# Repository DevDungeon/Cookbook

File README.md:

## The Cookbook Method

A cookbook in the programming context is collection of tiny programs that each demonstrate a particular programming concept. The Cookbook Method is the process of learning a programming language by building up a repository of small programs that implement specific programming concepts. Starting with a Hello World program and building the knowledge piece by piece on top of that.

If you are a beginner, you will probably want to start out with one language like Python and start building up your repetoire of snippets for reference and confidence. If you are a seasoned developer, you may want to start building a cookbook from scratch for a new language you have never used, or keep a cookbook for more advanced topics in a language you are already familiar with.

Here is an example of when my Cookbook comes in handy. Recently I was faced with a situation where I needed to make an HTTP request to an API, parse the JSON response, generate a CSV spreadsheet, and email the spreadsheet. Because I already had my own cookbook snippets for doing each of those three actions, it was really easy to put together a program that did what I needed it to.

## Watch the video

### Benefits of Building Your Own Cookbook

* You can share it with others
* Learn topics that are interesting to you
* You build up your knowledge in small increments
* You can see your progress over time
* You have a library of reference material in your own style.
* It is quicker than looking up documentation or looking for a Stack Overflow answer.
* Explore new topics
* Learn new programming languages.
* Tips for Building a Cookbook
* Store your cookbook in a version control system like Git.
* Keep a to do list of topics or programming languages you want to explore and learn
* It does not have to be just code. I have a lot of plain text .txt files with notes on things like how to create a Python pip package, creating Ruby Gems, or how to create a runnable JAR in Java. Sometimes tips on installing prerequisites if something was difficult or just notes on how to compile and run programs.
* It can also be template programs. For example I have a base chrome browser extension that doesn't really do anything itself, but it is a fully functional extension with all the boilerplate done and ready for me to start developing.
* Programs should be fully runnable and not just chunks of code without context that do not compile and execute
* Keep the snippets small, simple and to one topic

### Example Cookbook Topics

Everyone has different goals with programming so identify topics relevant to your interests. Here are some ideas if you do not know where to get started.

* Hello, world
* Getting user input from stdin
* Taking command line arguments
* Reading and writing files
* Using TCP sockets
* Making HTTP requests
* Parsing JSON
* Creating a CSV file
* Making database connections
* Playing an audio file
* Multithreading
* Drawing 2D graphics to screen
* Drawing 3D graphics to screen
* GUI programming

## The DevDungeon Cookbook

* http://www.devdungeon.com/cookbook
* https://github.com/DevDungeon/Cookbook

## Contact

John "NanoDano" Leon <nanodano@devdungeon.com>
https://www.devdungeon.com

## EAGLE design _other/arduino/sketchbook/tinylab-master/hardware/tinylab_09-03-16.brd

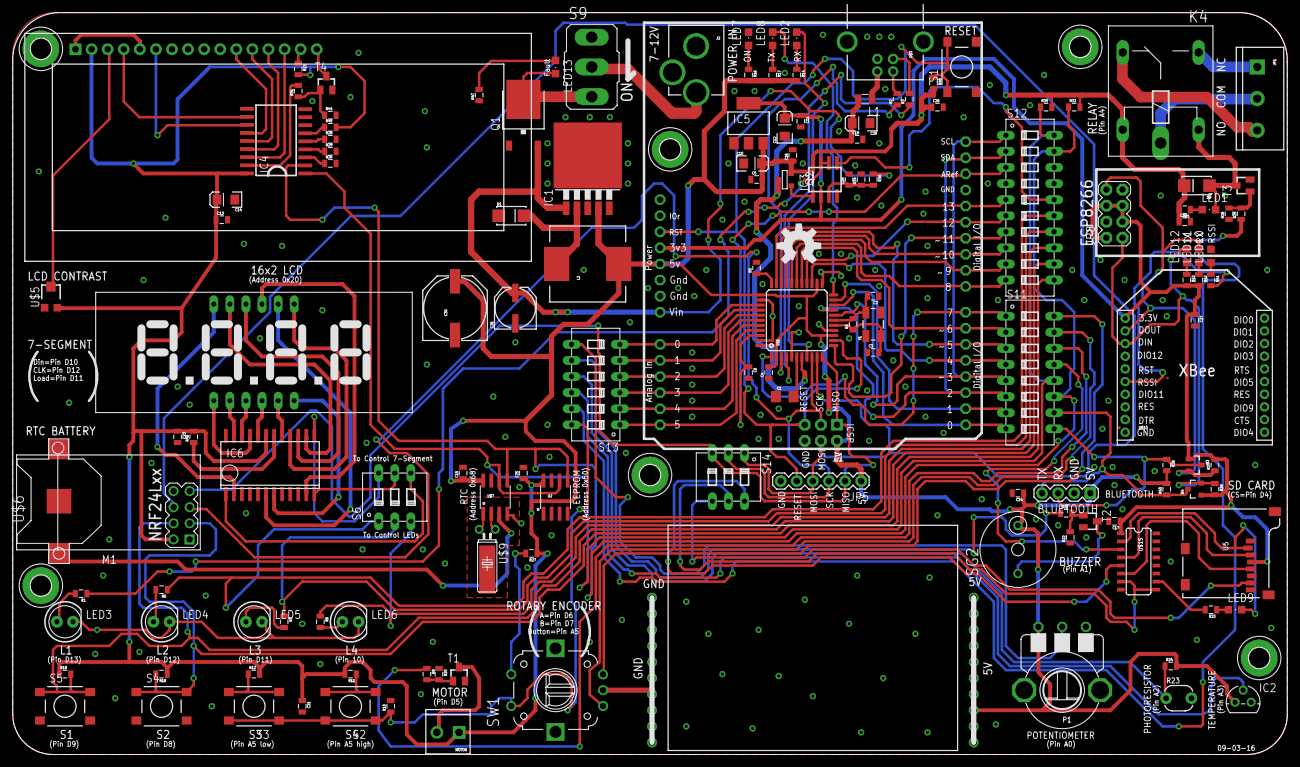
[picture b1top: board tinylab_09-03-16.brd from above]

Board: 2 copper layers, 201.3 x 117.2 mm, 151 parts (0 on the bottom side), 136 nets.

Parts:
BLUETOOTH: 1X04
C1: 1uF; 1206
C2, C3: 22pF; 0805
C4, C5, C6, C11, C15, C16, C17, C18, C19, C21, C22, C24, C25, C26, C27: 100nF; 0805
C10, C12, C20: 10uF; EIA3216
C13, C23: 100nf; 0805
C14: 10uf; EIA3216
C28: 100uF; NIPPON_F80
C30: 470uF; PANASONIC_G
D1, D2: 1N4007; SMA-DIODE_ALT
H1, H2, H3, H4, H5, H6: MOUNT-PAD-ROUND3.2; 3,2-PAD
IC1: LM2575S; TO263-5
IC2: LM35CZ; TO92
IC3: LM358MX; SO08
IC4: MCP2300X/SO; SO18W
IC5: LD117AS33TR; SOT223
IC6: MAX7219CWG; SO24W
J1: AVR_SPI_PRG_6NS; 2X3-NS
J2: POWER_JACKPTH_LOCK; POWER_JACK_PTH_LOCK
JP1: SCREWTERMINAL-5MM-3
JP5: 1X06
JP8: 2X4
K4: ZF112
L1: PTC0805
L2: CDRH125
LED1, LED9, LED12: Blue; CHIPLED_0805
LED2, LED8: Green; CHIPLED_0805
LED3, LED4, LED5, LED6: RED; LED5MM
LED7, LED10: Yellow; CHIPLED_0805
LED11, LED13: Red; CHIPLED_0805
M1: WIRELESS-NRF24L01
MOTOR: SCREWTERMINAL-3.5MM-2
P1: P120PK
Q1: FDD4141 or FDD6637; TO252
Q2: FDN340; SOT-23
Q3, Q4: BSS138; SOT23-3
R1, R6, R7, R8, R14, R16, R17: 330; 0805
R2, R3: 22; 0805
R4: 1M; 0805
R5, R34, R36, R37, R38, R39, R40: 10K; 0805
R9, R10, R11, R15, R21, R25, R31, R33, R47: 1k; 0805
R12: 3.9k; 0805
R13: 100R; 0805
R18, R19, R20, R22, R24, R26, R27, R28, R29, R30, R44, R45, R48: 10k; 0805
R23: PHOTOCELLPTH-KIT; PHOTOCELL-KIT
R32, R35: 4.7k; 0805
R41, R42, R43: 1K; 0805
R46: 30k; 0805
S1, S2, S3, S4, S5: DTSM-6
S6, S14: DIP03YL
S9: M9040P
S11: DIP08YL
S12: DIP10YL
S13: DIP06YL
SG2: BMT1205XH7.5
SW1: ENCODER_SW1-PEC12; PEC12_INCREMENTAL_ENCODER
T1, T2, T3, T4: BC847; SOT23-BEC
U1: LCD-16X2SILK; LCD-16X2
U2: 24LC256; SO08
U5: USD-SOCKETNEW; MICRO-SD-SOCKET-PP
U$1: ATMEGA32U4TQFP-44; TQFP44
U$2: BREADBOARDMINI; BREADBOARD-MINI
U$3: USB+SHIELD; USB-B-PTH
U$4: UNO_R3
U$5: 10k; TC33X
U$6: CR1220-SMD
U$7: DS1307SO8; SO08
U$9: CRYSTAL_GNDPAD; TC38H_GNDPAD
U$10: XBEE-1B2; XBEE-SILK
U$11: TINYLAB_LOGO_LARGE
U$13: MYLIB_LCQ_4D_7SEG; MYLIB_LDQ_4D_7SEG
U$14: OSHW-LOGO-L
U$15: 74HC4050; SO016
Y1: 16Mhz; CRYSTAL-SMD-5X3

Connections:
3.3V: C11.1, C12.A, C17.1, C27.1, IC3.2, IC5.4, JP8.2, JP8.3, JP8.5, JP8.6, Q3.1, Q4.1, R37.2, R39.2, R42.2, R43.2, U5.4, U$4.3V, U$10.1, U$15.1
4: S11.4, U$1.25, U$4.D4
5: S11.3, U$1.31, U$4.D5
6: S11.2, U$1.27, U$4.D6
7: S11.1, U$1.1, U$4.D7
8: S12.10, U$1.28, U$4.D8
9: S12.9, U$1.29, U$4.D9
10: S12.8, U$1.30, U$4.D10
11: S12.7, U$1.12, U$4.D11
12: S12.6, U$1.26, U$4.D12
13: S12.5, U$1.32, U$4.D13
!RESET: J1.5, JP5.5, R48.1, S1.1, S1.2, U$1.13, U$4.RESET
+5V: BLUETOOTH.1, C4.2, C5.2, C10.A, C13.1, C14.A, C15.1, C16.1, C21.1, C22.1, C23.1, C24.1, C25.1, C26.1, C30.+, D2.C, IC1.4, IC2.1, IC3.8, IC4.18, IC5.3, IC6.19, J1.2, JP5.1, K4.1, L2.2, M1.2, MOTOR.1, P1.E, Q2.2, R11.2, R12.2, R13.2, R14.2, R15.2, R16.2, R17.2, R18.1, R19.1, R24.2, R27.1, R32.2, R35.2, R38.2, R40.2, R45.2, R46.2, R48.2, SG2.+, U1.2, U2.8, U$1.2, U$1.14, U$1.24, U$1.34, U$1.44, U$4.5V, U$5.3, U$7.8
A0: P1.S, S13.7
A1: R21.1, S13.8
A2: R23.1, R24.1, S13.9
A3: IC2.2, S13.10
A4: R25.1, S13.11
A5: R10.1, S2.1, S2.2, S3.1, S3.2, S13.12, SW1.P1
A_A0: S13.6, U$1.36, U$4.A0
A_A1: S13.5, U$1.37, U$4.A1
A_A2: S13.4, U$1.38, U$4.A2
A_A3: S13.3, U$1.39, U$4.A3
A_A4: S13.2, U$1.40, U$4.A4
A_A5: S13.1, U$1.41, U$4.A5
A_AREF: C6.1, S12.3, U$1.42, U$4.AREF
A_MISO: J1.1, JP5.2, M1.7, S14.3, U$1.11
A_MOSI: J1.4, JP5.4, M1.6, S14.1, U$1.10
A_RX: S11.8, U$1.20, U$4.D0
A_SCK: J1.3, JP5.3, M1.5, S14.2, U$1.9
A_SCL: S11.5, S12.1, U$1.18, U$4.D3, U$4.SCL
A_SDA: S11.6, S12.2, U$1.19, U$4.D2, U$4.SDA
A_TX: S11.7, U$1.21, U$4.D1
D4: S11.13, U$15.3
D5: R9.1, S11.14
D6: S11.15, SW1.A
D7: S11.16, SW1.B
D8: M1.3, R18.2, S4.1, S4.2, S12.11
D9: M1.4, R19.2, S5.1, S5.2, S12.12
D10: R8.1, S6.3, S12.13
D11: R7.1, S6.2, S12.14
D12: R6.1, S6.1, S12.15
D13: IC3.5, S12.16
D+: R3.1, U$1.4
D-: R2.1, U$1.3
DB4: IC4.13, U1.11
DB5: IC4.14, U1.12
DB6: IC4.15, U1.13
DB7: IC4.16, U1.14
DIN: JP8.1, LED12.C, Q4.2, R39.1, U$10.3
DOUT: JP8.8, LED11.C, Q3.2, R37.1, U$10.2
E: IC4.12, U1.6
GND: BLUETOOTH.2, C1.1, C2.1, C3.1, C4.1, C5.1, C6.2, C10.C, C11.2, C12.C, C13.2, C14.C, C15.2, C16.2, C17.2, C18.2, C19.2, C20.C, C21.2, C22.2, C23.2, C24.2, C25.2, C26.2, C27.2, C28.-, C30.-, D1.A, IC1.3, IC1.5, IC1.GND, IC2.3, IC3.4, IC4.9, IC5.1, IC6.4, IC6.9, J1.6, J2.GND, J2.GNDBREAK, JP5.6, JP8.7, LED3.K, LED4.K, LED5.K, LED6.K, LED7.C, LED10.C, M1.1, P1.A, Q1.1, R5.2, R10.2, R20.1, R22.1, R23.2, R26.1, R28.2, R29.2, R30.2, R34.2, R44.2, R47.1, S1.3, S1.4, S4.3, S4.4, S5.3, S5.4, S12.4, S12.17, SW1.C, T1.E, T2.E, T3.E, T4.E, U1.1, U1.5, U2.1, U2.2, U2.3, U2.4, U2.7, U5.6, U5.CD1, U5.CD2, U5.GND1, U5.GND3, U$1.5, U$1.15, U$1.23, U$1.35, U$1.43, U$3.GND, U$3.S1, U$3.S2, U$4.GND, U$4.GND1, U$4.GND2, U$5.1, U$6.-, U$7.4, U$9.P$1, U$10.10, U$15.8, U$15.11, U$15.14
LED: R33.2, U$15.10
LIGHT: IC4.17, R31.2
MISO: S14.4, U5.7
MOSI: S14.6, U$15.5
unnamed: R2.2, U$3.D-
unnamed: R3.2, U$3.D+
unnamed: LED3.A, R1.2
unnamed: C1.2, U$1.6
unnamed: R11.1, S2.3, S2.4
unnamed: C3.2, R4.1, U$1.16, Y1.1
unnamed: C2.2, R4.2, U$1.17, Y1.3
unnamed: R21.2, R22.2, T2.B
unnamed: R5.1, U$1.33
unnamed: D1.C, IC1.2, L2.1
unnamed: R12.1, S3.3, S3.4
unnamed: R9.2, R20.2, T1.B
unnamed: LED4.A, R6.2
unnamed: JP1.3, K4.O
unnamed: LED5.A, R7.2
unnamed: MOTOR.2, T1.C
unnamed: LED6.A, R8.2
unnamed: SG2.-, T2.C
unnamed: LED1.A, R15.1
unnamed: R25.2, R26.2, T3.B
unnamed: D2.A, K4.2, LED1.C, T3.C
unnamed: LED2.A, R14.1
unnamed: LED8.A, R17.1
unnamed: JP1.2, K4.P
unnamed: JP1.1, K4.S
unnamed: J2.PWR, S9.2
unnamed: LED13.C, Q1.3, S9.3
unnamed: IC4.5, R28.1
unnamed: IC4.4, R29.1
unnamed: IC4.3, R30.1
unnamed: R27.2, SW1.P2
unnamed: R31.1, R44.1, T4.B
unnamed: U1.3, U$5.2
unnamed: T4.C, U1.16
unnamed: U$7.2, U$9.1
unnamed: U$6.+$1, U$7.3
unnamed: IC6.14, U$13.11
unnamed: U5.3, U$15.4
unnamed: U5.5, U$15.6
unnamed: U$7.1, U$9.2
unnamed: LED9.A, R33.1
unnamed: LED9.C, U5.2, U$15.2
unnamed: L1.1, U$3.VBUS
unnamed: C18.1, IC3.3, R34.1, R36.2
unnamed: LED10.A, R41.1
unnamed: IC3.1, Q2.3
unnamed: IC3.6, IC3.7, R1.1
unnamed: LED11.A, R42.1
unnamed: LED12.A, R43.1
unnamed: LED13.A, R47.2
unnamed: IC4.6, R45.1
unnamed: IC6.18, R46.1
unnamed: IC6.16, U$13.7
unnamed: IC6.20, U$13.4
unnamed: IC6.23, U$13.2
unnamed: IC6.21, U$13.1
unnamed: IC6.15, U$13.10
unnamed: IC6.17, U$13.5
unnamed: IC6.22, U$13.3
unnamed: IC6.7, U$13.6
unnamed: IC6.6, U$13.8
unnamed: IC6.11, U$13.9
unnamed: IC6.2, U$13.12
unnamed: R13.1, U1.15
unnamed: LED7.A, R16.1
RS: IC4.11, U1.4
RSSI: R41.2, U$10.6
RX: BLUETOOTH.3, Q3.3, R38.1, S11.9
RXLED: LED2.C, U$1.8
SCK: S14.5, U$15.7, U$15.9
SCL: IC4.1, R35.1, S11.12, S12.20, U2.6, U$7.6
SDA: IC4.2, R32.1, S11.11, S12.19, U2.5, U$7.5
S_D10: IC6.1, S6.4
S_D11: IC6.12, S6.5
S_D12: IC6.13, S6.6
TX: BLUETOOTH.4, Q4.3, R40.1, S11.10
TXLED: LED8.C, U$1.22
VCC: C28.+, IC1.1, Q1.2, R36.1, U$4.VIN
VUSB: C19.1, C20.A, L1.2, Q2.1, U$1.7

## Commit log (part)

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2015-04-22 Initial commit. Adding all reference code under one repo
2015-04-26 Adding python blackhat udp and ping discovery
2015-04-26 Adding git ignore in python to ignore .idea folder
2015-04-26 Adding sys_info.py with system info like platform, variable sizes, etc
2015-05-07 Adding gitignore to php drupal modules bitcoin_donation phpqrcode cache folder
2015-05-17 Adding android studio project files
2015-07-29 Adding a couple more samples
2015-08-14 Updating Ruby daemon example
2015-08-14 Adding file and dir manipulation in perl example
2015-08-14 Updating perl exif example
2015-08-14 Updating hello world perl
2015-08-14 Adding image examples
2015-08-14 Updating haskell cmd arg example
2015-08-14 Updated coffeescript references
2015-08-14 Adding simplified webrtc audio example
2015-08-16 Adding updating C Pcap examples
2015-08-16 Updating packet capture examples with gopacket
2015-08-23 Adding file examples
2015-08-23 Updated file examples in Go
2015-09-20 misc updates. Removed chrome extension base since it is its own repo now
2015-09-20 Cleaning up some snippets. Updated bash references
2015-11-23 Adding references for binary data in python
2015-11-24 Adding some Perl HTTP and DOM references
2015-12-06 Adding Python Tkinter references
2015-12-09 Adding readme
2015-12-21 Adding my LAMP dashboard written in Python/GTK/Glade as an example
2015-12-24 Cleaning up and renaming a couple things
2016-01-02 Updating Python examples
2016-01-02 Adding some Java examples
2016-01-02 Adding example of a Java Jar with resources like images
2016-01-02 updating git ignore
2016-01-02 Adding SSH example with Jsch
2016-01-02 Adding Excel files example using POI
2016-01-02 Adding two examples: RedditClient which uses Apache Http client along with org.json library. SimpleJson is the same thing except uses the google code simple json library. They are similar not sure if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
2016-01-10 Maven project demonstrating how to create a mac .app
2016-01-15 Adding another simple SSL server example
2016-01-31 Adding example for Russian espeak text to speech
2016-02-01 Adding some basic Rust notes
2016-04-13 Adding some C++ Examples: sleep, random, ncurses, qt5+winpcap. Also Python ldap server example
2016-04-14 Adding compilation notes
2016-04-14 Minimal C example from the C bible
2016-04-16 Adding examples to count characters and lines
2016-04-16 Adding example of counting words, lines, and characters]
2016-04-16 Adding more C examples
2016-04-16 Even more C examples
2016-04-17 Fix bug in qsort output and add void pointer cast example.
2016-04-23 Adding some bindshell examples and info on adding Icon to Windows GCC .exe
2016-05-08 Adding misc snippets that were laying around
2016-07-16 Adding spreadsheet examples with CSV and XLSX
2016-07-22 Adding selenium screenshot examples
2016-07-31 Adding Android examples: contact list, disk space checker. Go mongo example, python selenium and extract pngs from binary files. Python spreadsheet examples. Ruby selenium example
2016-10-06 Updating Java Pcap example so the maven file creates a jar and a shaded(uber) jar so it runs as a standalone
2016-10-06 Changing required jvm from 1.8 to 1.7 in 2d example
2016-10-14 Adding ability to use multiple icons and let the JVM decide on the best.
2016-10-14 Adding Desktop Demos
2016-10-15 Adding latest examples
2016-11-18 Tweaks
2016-11-18 Adding some neopixel examples
2016-12-02 Updating Python Selenium screenshot example. Updating Java SSH examples
2017-10-20 Adding Philips Hue light programming notes. Updated notes for static compiling Go programs for Docker containers
2017-10-21 Adding BitCoin Python price checker and Discord Bot Webhook example
2018-02-20 Adding discord bot example
2018-02-24 Updating samples
2018-03-05 Notes
2018-03-05 Adding new c++ stuff
2018-03-05 Adding make and cmake examples
2018-03-05 Adding simple libfunctions library example
2018-03-06 Adding c++ examples
2018-03-10 Adding bytes examples
2018-03-25 Adding Go web scraping examples
2018-03-25 Adding new C++ examples
2018-07-14 Adding AWS, OpenSCAD, Raspberry Pi, and Python example!
2018-09-11 Updaing notes about managing letsencrypt certs
2018-09-11 Adding JS Discord bot examples
2018-10-02 Adding Python text-to-speech, Java properties files
2018-10-06 Cleaning up Java directory
2018-10-16 Reorganizing, putting more tutorials
2018-10-29 Refactoring
2019-02-16 moving around
2019-02-27 Adding rust cross-compiling example
2019-02-27 Adding Rust/C wrapping and linking examples
2019-02-27 Updating todo list
2019-03-02 Adding python web scraping examples
2019-03-02 Removing incomplete docs
2019-03-20 Adding notes about Crystal language
2019-03-21 Adding cordova notes
2019-03-23 Adding get_file_metadata program
2019-03-23 Adding dump_hex example
2019-03-24 Adding find ascii in file application
2019-03-24 Adding find_file_signatures application
2019-03-29 Adding Selenium notes
2019-04-04 Adding vim notes
2019-04-04 Adding vscode notes
2019-04-10 Adding several examples
    - Python curses examples
    - RAspberry pi timelapse photo taker
    - reStructuredText example
    - Ruby getpass and ssh examples
2019-04-10 Adding Maven m2 settings example for Java
2019-04-24 Added Base64, echoing, functions, aliases
    I also fixed the indentation and spacing in a way that now makes sense. I also posted a link to a documentation website listing all standard Powershell commands.
2019-05-23 Fixing Ruby GTK+3 examples
2019-05-23 Adding qt systray icon and dialog examples
2019-08-20 Adding kivy android notes
2019-09-09 Latest updateS
2019-09-13 Flask examples
2020-02-11 Added wxpython pip notes
2020-03-02 adding python sqlite examples
2020-03-14 adding pymysql examples
2020-03-14 Adding python IMAP read mail examples
2020-03-15 Adding from/to/priority output of reading mail
2020-03-15 Adding Python FTP examples
2020-03-16 Adding Python SSH examples
2020-06-01 Adding log rotate example for Python
2020-06-15 Removing old languages and examples
2020-10-12 Bump junit from 3.8.1 to 4.13.1 in /java/ServletExamples/mvnhelloservlet
    Bumps [junit](https://github.com/junit-team/junit4) from 3.8.1 to 4.13.1.
    - [Release notes](https://github.com/junit-team/junit4/releases)
    - [Changelog](https://github.com/junit-team/junit4/blob/main/doc/ReleaseNotes4.13.1.md)
    - [Commits](https://github.com/junit-team/junit4/commits/r4.13.1)
2020-10-13 Bump junit from 3.8.1 to 4.13.1 in /java/SendMailExample
    Bumps [junit](https://github.com/junit-team/junit4) from 3.8.1 to 4.13.1.
    - [Release notes](https://github.com/junit-team/junit4/releases)
    - [Changelog](https://github.com/junit-team/junit4/blob/main/doc/ReleaseNotes4.13.1.md)
    - [Commits](https://github.com/junit-team/junit4/commits/r4.13.1)
2021-01-14 Bump poi from 3.11 to 3.17 in /java/ExcelFiles
    Bumps poi from 3.11 to 3.17.
2021-03-08 Adding back lots of old stuff
2021-04-09 Adding cPanel API email management examples
2021-06-04 Bump httpclient from 4.5.1 to 4.5.13 in /java/SimpleJson
    Bumps httpclient from 4.5.1 to 4.5.13.
    ---
    updated-dependencies:
    - dependency-name: org.apache.httpcomponents:httpclient
    dependency-type: direct:production
    ...
2021-06-04 Bump httpclient from 4.5.1 to 4.5.13 in /java/HttpExamples
    Bumps httpclient from 4.5.1 to 4.5.13.
    ---
    updated-dependencies:
    - dependency-name: org.apache.httpcomponents:httpclient
    dependency-type: direct:production
    ...
2021-06-04 Bump httpclient from 4.5.1 to 4.5.13 in /java/RedditClient
    Bumps httpclient from 4.5.1 to 4.5.13.
    ---
    updated-dependencies:
    - dependency-name: org.apache.httpcomponents:httpclient
    dependency-type: direct:production
    ...
2021-06-14 Adding Java file examples to join paths, get home dir and absolute paths
2021-06-19 Updating pyqt5 webengine example
2021-10-14 Adding extract_images_from_pdf
2021-12-28 Adding expressjs example?
2021-12-28 Adding sockets.io example
2022-01-24 Adding email smtp example forPHP
2022-02-01 Adding more examples
2022-02-06 Updated notes on mounting smb drives
2022-02-06 fixed pyqt5 webview example
2022-02-06 Create conkyrc
2022-02-12 Adding java-jar-runner.desktop
2022-02-13 Removing and omitting built file
2022-02-15 more examples
2022-02-15 Adding google font example
2022-02-18 Testing custom framework
2022-02-18 Stable working micro framework
2022-02-19 Adding port scan examples. Adding php custom framework
2022-02-28 Adding example of how to make bootable floppy/ISO from an assembly file
2022-03-19 lots of c, c++, and freepascal examples
2022-03-20 some curses/sfml/gtk updates
2022-03-22 sfml2 examples and template
2022-03-30 Adding math examples
2022-04-02 Bump minimist from 1.2.5 to 1.2.6 in /node.js
    Bumps [minimist](https://github.com/substack/minimist) from 1.2.5 to 1.2.6.
    - [Release notes](https://github.com/substack/minimist/releases)
    - [Commits](https://github.com/substack/minimist/compare/1.2.5...1.2.6)
    ---
    updated-dependencies:
    - dependency-name: minimist
2022-06-22 Bump sqlite3 from 5.0.2 to 5.0.3 in /node.js
    Bumps [sqlite3](https://github.com/TryGhost/node-sqlite3) from 5.0.2 to 5.0.3.
    - [Release notes](https://github.com/TryGhost/node-sqlite3/releases)
    - [Changelog](https://github.com/TryGhost/node-sqlite3/blob/master/CHANGELOG.md)
    - [Commits](https://github.com/TryGhost/node-sqlite3/compare/v5.0.2...v5.0.3)
    ---
    updated-dependencies:
2022-07-06 Bump jsch from 0.1.51 to 0.1.54 in /java/SshExample
    Bumps jsch from 0.1.51 to 0.1.54.
    ---
    updated-dependencies:
    - dependency-name: com.jcraft:jsch
    dependency-type: direct:production
    ...
2022-11-10 Bump socket.io-parser from 4.0.4 to 4.0.5 in /node.js
    Bumps [socket.io-parser](https://github.com/socketio/socket.io-parser) from 4.0.4 to 4.0.5.
    - [Release notes](https://github.com/socketio/socket.io-parser/releases)
    - [Changelog](https://github.com/socketio/socket.io-parser/blob/main/CHANGELOG.md)
    - [Commits](https://github.com/socketio/socket.io-parser/compare/4.0.4...4.0.5)
    ---
    updated-dependencies:
2022-11-22 Bump engine.io and socket.io in /node.js
    Bumps [engine.io](https://github.com/socketio/engine.io) to 6.2.1 and updates ancestor dependency [socket.io](https://github.com/socketio/socket.io). These dependencies need to be updated together.
    Updates `engine.io` from 6.1.3 to 6.2.1
    - [Release notes](https://github.com/socketio/engine.io/releases)
    - [Changelog](https://github.com/socketio/engine.io/blob/main/CHANGELOG.md)
    - [Commits](https://github.com/socketio/engine.io/compare/6.1.3...6.2.1)
    Updates `socket.io` from 4.4.1 to 4.5.3
2023-03-13 Bump sqlite3 from 5.0.2 to 5.1.5 in /node.js
    Bumps [sqlite3](https://github.com/TryGhost/node-sqlite3) from 5.0.2 to 5.1.5.
    - [Release notes](https://github.com/TryGhost/node-sqlite3/releases)
    - [Commits](https://github.com/TryGhost/node-sqlite3/compare/v5.0.2...v5.1.5)
    ---
    updated-dependencies:
    - dependency-name: sqlite3
2023-04-14 Bump json from 20151123 to 20230227 in /java/JsonExample
    Bumps [json](https://github.com/douglascrockford/JSON-java) from 20151123 to 20230227.
    - [Release notes](https://github.com/douglascrockford/JSON-java/releases)
    - [Changelog](https://github.com/stleary/JSON-java/blob/master/docs/RELEASES.md)
    - [Commits](https://github.com/douglascrockford/JSON-java/commits)
    ---
    updated-dependencies:
2023-04-14 Bump json from 20151123 to 20230227 in /java/RedditClient
    Bumps [json](https://github.com/douglascrockford/JSON-java) from 20151123 to 20230227.
    - [Release notes](https://github.com/douglascrockford/JSON-java/releases)
    - [Changelog](https://github.com/stleary/JSON-java/blob/master/docs/RELEASES.md)
    - [Commits](https://github.com/douglascrockford/JSON-java/commits)
    ---
    updated-dependencies:
2023-05-03 Bump engine.io and socket.io in /node.js
    Bumps [engine.io](https://github.com/socketio/engine.io) to 6.4.2 and updates ancestor dependency [socket.io](https://github.com/socketio/socket.io). These dependencies need to be updated together.
    Updates `engine.io` from 6.1.3 to 6.4.2
    - [Release notes](https://github.com/socketio/engine.io/releases)
    - [Changelog](https://github.com/socketio/engine.io/blob/main/CHANGELOG.md)
    - [Commits](https://github.com/socketio/engine.io/compare/6.1.3...6.4.2)
    Updates `socket.io` from 4.4.1 to 4.6.1
2024-05-01 Update vimrc
    Adding some comments and notes on tabs vs spaces
2026-05-28 Adding turbo pascal folder
2026-05-28 Adding a couple turbo pascal examples

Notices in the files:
_other/arduino/sketchbook/tinylab-master/hardware/tinylab_09-03-16.brd:
Released under the GNU-GPL v2
parts and their libraries:
SparkFun-DigitalIC: Licensing: CC v3.0 Share-Alike You are welcome to use this library for commercial purposes.
SparkFun-Connectors: Licensing: Creative Commons ShareAlike 4.0 International - https://creativecommons.org/licenses/by-sa/4.0
